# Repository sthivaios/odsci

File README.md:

# ODSCI

<div align="center">

  <h2 style="font-weight: bold;">An STM32-based USB interface for DS18B20 temperature sensors</h2>
  
</div>

## Getting Started - How to use ODSCI

**If you want to get started using ODSCI quickly, and don't care about the project, this is the only section of the README that matters to you.**

You can grab a pre-built CLI binary from the releases page for your platform/OS, or build from source. The CLI is written in Go and is located in the `/cli` directory.

Connect the ODSCI probe to your computer, and find the serial port that it uses (COM port on Windows, or a /dev/tty device on Linux and MacOS).

Then, you can use the `capture` command to save a given amount of samples as a CSV file.

```shell
./odsci --port THE_SERIAL_PORT_HERE --samples 100 --interval 10 --output "./output.csv"
```

The CLI has more features than just the `capture` command. Run `./odsci --help` for more information on the commands, or read the documentation.

## Introduction

ODSCI is an STM32-based USB interface for DS18B20 sensors. It stands for **O**neWire **DS**18B20 **C**omputer **I**nterface.

It connects to any computer through a USB-C port and exposes a USB CDC virtual serial port, through which
the MCU can send temperature readings back to the computer.

I am mainly working on this project, in order to teach myself Go (which the CLI uses), while also using it as
an excuse to attempt to write my own OneWire "driver" for the STM32 to communicate with the sensor.

## Project structure

You can find each "part" of ODSCI in its corresponding folder.

1. The firmware that runs on the STM32 is written in C and configured with CubeMX and uses CMake. It is located in the `/firmware` directory.

2. The hardware (PCB) is a KiCad project. It is located under `/hardware`.

3. The enclosure was designed in Fusion360. The project file, as well as any STL exports are located under the `/enclosure`.

4. The CLI is written in Go. You can find its source under `/cli`. I will attempt to cross-compile it for different platforms. Check the repo releases for pre-built binaries.

5. The docs are written with VitePress. You can find them under `/docs`.

## Contributing

You are welcome to report any issues that you find with any part of ODSCI, or open pull requests to fix them.

If you are actually contributing code to the project, make sure that you understand the license terms.

## Licensing

Different parts of the project are licensed under different licenses.

Under each directory, you will find a separate LICENSE file for that part of the project.

While that may seem a little confusing at first, please understand that some parts like the PCB simply
aren't very compatible with the usual licenses like MIT, GPL, etc.

See [LICENSE](LICENSE) for more info.

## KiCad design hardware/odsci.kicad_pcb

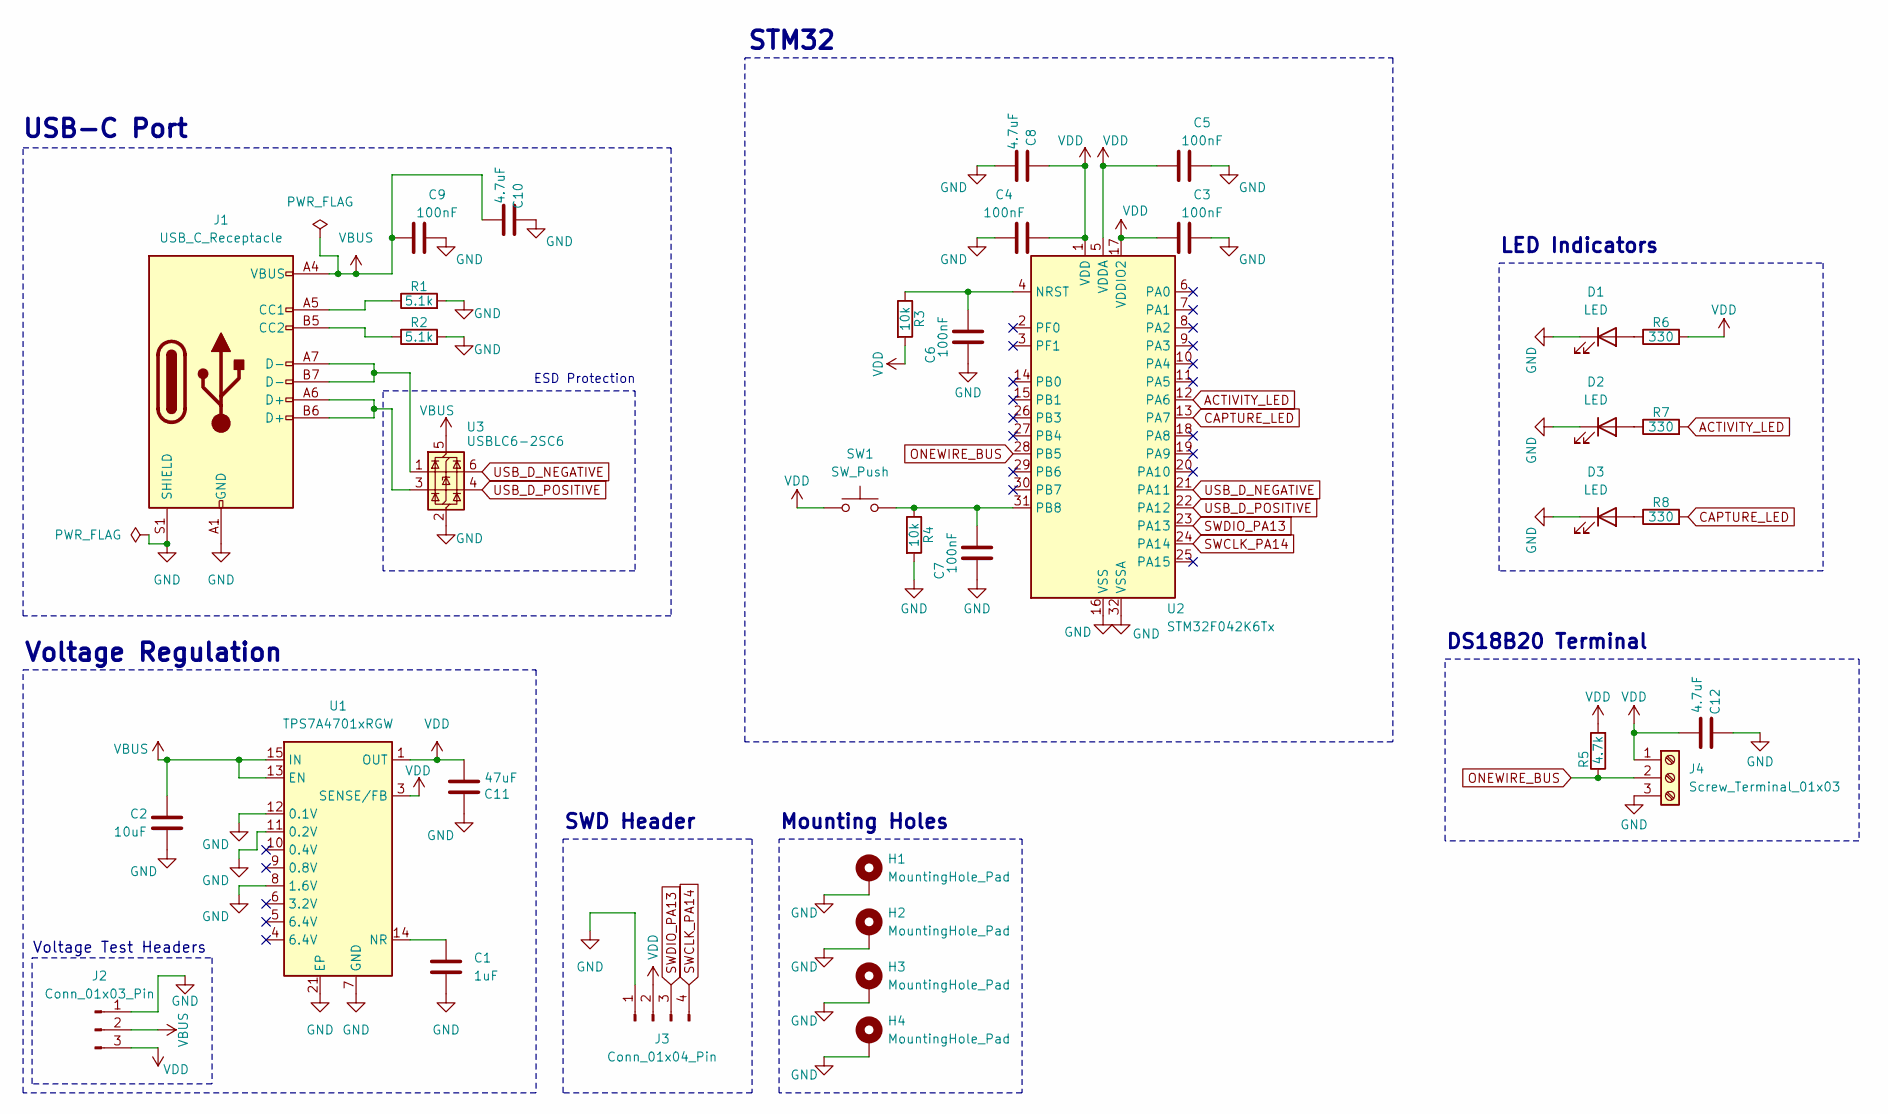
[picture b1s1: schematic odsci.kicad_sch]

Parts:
C1: 1uF; C_0805_2012Metric; LCSC C28323
C2: 10uF; C_0805_2012Metric; LCSC C15850
C3, C4, C5, C6, C7, C9: 100nF; C_0402_1005Metric; LCSC C1525
C8, C10, C12: 4.7uF; C_0805_2012Metric; LCSC C1779
C11: 47uF; C_0805_2012Metric; LCSC C16780
D1, D2, D3: LED; LED_D3.0mm
H1, H2, H3, H4: MountingHole_Pad; MountingHole_2.2mm_M2_Pad
J1: USB_C_Receptacle; USB_C_Receptacle_GCT_USB4105-xx-A_16P_TopMnt_Horizontal; LCSC C3020560
J2: Conn_01x03_Pin; PinHeader_1x03_P2.54mm_Vertical; LCSC C2915006
J3: Conn_01x04_Pin; PinHeader_1x04_P2.54mm_Vertical; LCSC C5184785
J4: Screw_Terminal_01x03; TerminalBlock_Phoenix_MPT-0,5-3-2.54_1x03_P2.54mm_Horizontal; LCSC C5288763
R1, R2: 5.1k; R_0402_1005Metric; LCSC C25905
R3, R4: 10k; R_0402_1005Metric; LCSC C25744
R5: 4.7k; R_0402_1005Metric; LCSC C25900
R6, R7, R8: 330; R_0402_1005Metric; LCSC C25104
SW1: SW_Push; SW_SPST_Omron_B3F-315x_Angled; LCSC C231320
U1: TPS7A4701xRGW; Texas_RGW0020A_VQFN-20-1EP_5x5mm_P0.65mm_EP3.15x3.15mm_Ther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; LCSC C90084
U2: STM32F042K6Tx; LQFP-32_7x7mm_P0.8mm; LCSC C69216
U3: USBLC6-2SC6; SOT-23-6; LCSC C7519

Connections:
ACTIVITY_LED: R7.2, U2.12 (PA6)
CAPTURE_LED: R8.2, U2.13 (PA7)
GND: C1.1, C2.1, C3.1, C4.1, C5.1, C6.2, C7.2, C8.1, C9.1, C10.2, C11.2, C12.2, D1.1 (K), D2.1 (K), D3.1 (K), H1.1, H2.1, H3.1, H4.1, J1.A1 (GND), J1.A12 (GND), J1.B1 (GND), J1.B12 (GND), J1.S1 (SHIELD), J2.1, J3.1, J4.3, R1.2, R2.2, R4.2, U1.7 (GND), U1.8 (1.6V), U1.11 (0.2V), U1.12 (0.1V), U1.21 (EP), U2.16 (VSS), U2.32 (VSSA), U3.2 (GND)
unnamed: D1.2 (A), R6.1
unnamed: D2.2 (A), R7.1
unnamed: D3.2 (A), R8.1
unnamed: J1.A5 (CC1), R1.1
unnamed: J1.B5 (CC2), R2.1
unnamed: J1.A6 (D+), J1.B6 (D+), U3.3 (I/O2)
unnamed: J1.A7 (D-), J1.B7 (D-), U3.1 (I/O1)
unnamed: C1.2, U1.14 (NR)
unnamed: C6.1, R3.1, U2.4 (NRST)
unnamed: C7.1, R4.1, SW1.2, U2.31 (PB8)
ONEWIRE_BUS: J4.2, R5.1, U2.28 (PB5)
SWCLK_PA14: J3.4, U2.24 (PA14)
SWDIO_PA13: J3.3, U2.23 (PA13)
USB_D_NEGATIVE: U2.21 (PA11), U3.6 (I/O1)
USB_D_POSITIVE: U2.22 (PA12), U3.4 (I/O2)
VBUS: C2.2, C9.2, C10.1, J1.A4 (VBUS), J1.A9 (VBUS), J1.B4 (VBUS), J1.B9 (VBUS), J2.2, U1.13 (EN), U1.15 (IN), U1.16 (IN), U3.5 (VBUS)
VDD: C3.2, C4.2, C5.2, C8.2, C11.1, C12.1, J2.3, J3.2, J4.1, R3.2, R5.2, R6.2, SW1.1, U1.1 (OUT), U1.3 (SENSE/FB), U1.20 (OUT), U2.1 (VDD), U2.5 (VDDA), U2.17 (VDDIO2)

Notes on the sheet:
STM32
ESD Protection
USB-C Port
Voltage Regulation
Voltage Test Headers
LED Indicators
SWD Header
Mounting Holes
DS18B20 Terminal

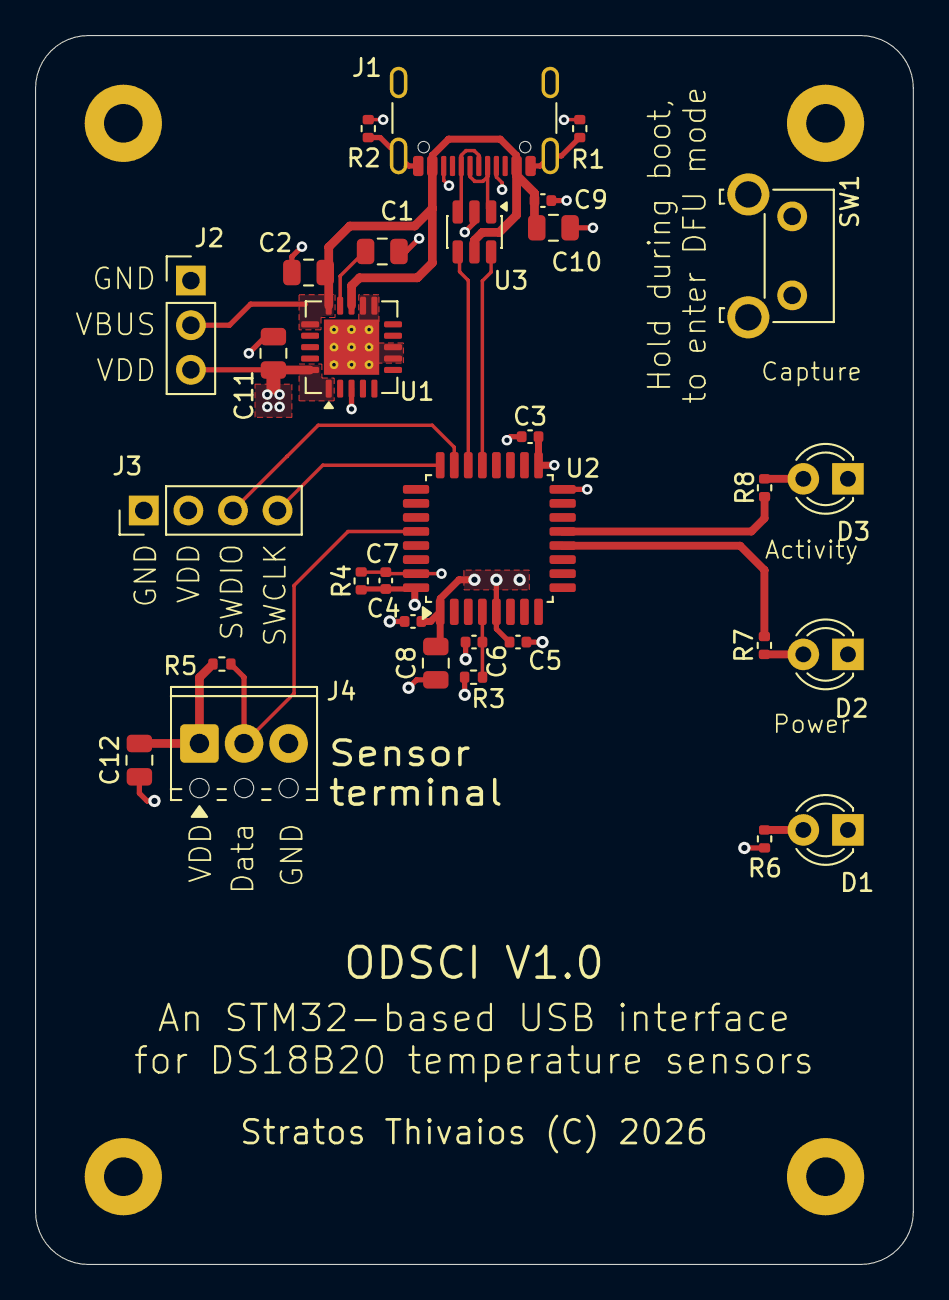
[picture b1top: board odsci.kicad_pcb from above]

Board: 4 copper layers, 50.0 x 70.0 mm, 35 parts (0 on the bottom side), 20 nets.

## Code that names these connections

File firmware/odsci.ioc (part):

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Mcu.Name=STM32F042K(4-6)Tx
Mcu.Package=LQFP32
Mcu.UserName=STM32F042K6Tx
PA11.Mode=Device
PA11.Signal=USB_DM
PA12.Mode=Device
PA12.Signal=USB_DP
PA13.Mode=Serial_Wire
PA13.Signal=SYS_SWDIO
PA14.Mode=Serial_Wire
PA14.Signal=SYS_SWCLK
PA6.GPIOParameters=GPIO_Label
PA6.GPIO_Label=ACTIVITY_LED
PA6.Signal=GPIO_Output
PA7.GPIOParameters=GPIO_Label
PA7.GPIO_Label=CLED_OR_ERROR_LED
PA7.Signal=GPIO_Output
PB5.GPIOParameters=GPIO_Label
PB5.GPIO_Label=ONEWIRE_BUS
PB5.Signal=GPIO_Input
RCC.SYSCLKFreq_VALUE=48000000
RCC.SYSCLKSource=RCC_SYSCLKSOURCE_HSI48
board=custom

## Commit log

2026-03-15 init
2026-03-17 add firmware license file
2026-03-17 add gitignore in firmware dir and the CubeMX ioc file
2026-03-17 CubeMX generated files
2026-03-18 add onewire driver
2026-03-18 onewire_write_bit() and onewire_read_bit()
2026-03-18 onewire_write_byte() and onewire_read_byte()
2026-03-18 add the higher level onewire functions
2026-03-18 fix minor stuff
2026-03-18 fix dumb include issues
2026-03-18 try to read the sensor in main.c
2026-03-18 make temperature variable global
2026-03-18 oops i got rid of the HAL_Delay accidentally
2026-03-18 command handler now receives stuff
2026-03-19 attempt to handle a command
2026-03-19 add a HAL_Delay in the main loop
2026-03-19 includes and stuff
2026-03-19 add the "-u _printf_float" linker flag
2026-03-19 command error handling
2026-03-19 use strcasecmp instead of strcmp
2026-03-19 get_info version cmd
2026-03-19 handle commands
2026-03-19 copyright headers
2026-03-20 remove random unused var
2026-03-20 configure PA6 and PA7 for leds
2026-03-20 change led labels in mx
2026-03-20 led control
2026-03-20 cli: go.mod
2026-03-20 cli: init main.go
2026-03-20 cli: add license
2026-03-20 cli: go.sum and go.mod
2026-03-20 cli: cobra init
2026-03-20 add packages
2026-03-20 cli: rootcmd description and desclaimer footer
2026-03-20 cli: init capture cmd
2026-03-20 cli: show cmd for gpl details
2026-03-20 cli: dependencies
2026-03-20 cli: capture cmd working at a low level
2026-03-20 cli: error handling
2026-03-20 cli: scan command
2026-03-20 cli: file organization
2026-03-21 cli: exit capture cmd gracefully on ctrl+c
2026-03-21 cli: minor bug and typo
2026-03-21 firmware: change cdc descriptors, fix bug
2026-03-21 cli: export as csv
2026-03-21 hardware: init kicad project
2026-03-21 hardware: schematic completed
2026-03-21 hardware: route pcb
2026-03-21 hardware: add mounting holes to pcb
2026-03-22 hardware: add a few decoupling caps
2026-03-22 hardware: layout of pcb
2026-03-22 hardware: fix mounting hole positions
2026-03-22 hardware: fully reroute and change pcb's layout
2026-03-24 hardware: update silkscreen, tiny layout changes
2026-03-24 hardware and schematic: add LCSC part number for switch
2026-03-24 hardware and schematic: update USB-C connector LCSC part number
2026-03-25 hardware: fix position of LEDs on the pcb to match enclosure
2026-03-28 hardware and schematic: update STM32 LCSC part number
2026-03-29 add CLED_IS_FOR_ERRORS_INSTEAD symbol
2026-03-29 make CLED commands depend on the CLED_IS_FOR_ERRORS_INSTEAD symbol
2026-03-29 use error indicator in different places
2026-03-29 fix includes
2026-03-29 remove leftover test from usbd_cdc_if.c
2026-03-29 report the CLED_IS_FOR_ERRORS_INSTEAD flag in GET_INFO
2026-03-29 bump major version as its a breaking change
2026-03-29 add firmware release script
2026-03-29 configure cmake to export .bin and .hex too
2026-03-29 github actions: firmware-release.yaml
2026-03-29 github actions: firmware-release.yaml: use local runner
2026-03-29 firmware release script: use master not main as the default branch
2026-03-29 firmware release script: fix bug cause i suck at bash
2026-03-29 firmware release script: add tag annotation
2026-03-29 firmware release action: change working dir
2026-03-29 add crc.c file
2026-03-29 create crc8 function
2026-03-29 implement crc
2026-03-29 report crc error in terminal if crc error occurs
2026-03-29 firmware release action: bug fixes
2026-03-29 bump firmware version: 1.0.0 to 1.1.0
2026-03-29 firmware release workflow: more bugs, we love github actions lol
2026-03-29 firmware release workflow: permission issue
2026-03-29 firmware release workflow: rename files before releasing
2026-03-29 firmware release workflow: im dumb
2026-03-29 firmware release workflow: clearly workflows arent my thing, more issue fixes
2026-03-29 changelog
2026-03-29 update to the github firmware release workflow
2026-03-29 this is so embarrassing lol
2026-03-29 minor changes to the github workflow again
2026-03-29 Restore cli directory from old branch
2026-03-29 cli: add version command, add a cli-release workflow
2026-03-29 cli: trigger workflow on dispatch for testing
2026-03-29 cli: oopsie
2026-03-29 cli: remove the scan command
2026-03-29 cli: fix ci/cd
2026-03-29 cli: changelog
2026-03-29 cli: ci/cd change trigger to only work on cli tags
2026-03-29 cli: add release.sh helper script
2026-03-29 cli: fix small bug in the release.sh script
2026-03-29 cli: fix minor ci/cd awk bug
2026-03-29 cli: more ci/cd bugs lol yay
2026-03-29 cli: more ci/cd bugs
2026-03-29 cli: more ci/cd bugs lol
2026-03-29 cli: more ci/cd bugs, i need a devops engineer lol
2026-03-29 cli: more ci- yeah you get the idea
2026-03-29 ci/cd: bump go releaser version
2026-03-29 ci/cd: fix goreleaser config for v2
2026-03-29 ci/cd: im gonna die lmao
2026-03-29 ci/cd: do i even bother with this anymore
2026-03-29 ci/cd: this actually might be a goreleaser issue not mine
2026-03-30 ci/cd: custom cli workflow without goreleaser
2026-03-30 ci/cd: oops forgot to give it write perms
2026-03-30 ci/cd: also build the linux binary for the cli, not only darwin and windows
2026-03-30 cli: add the read command
2026-03-30 cli: restructure read command for better readability and make code reusable as a func
2026-03-31 cli: helper function to clear the serial buffer
2026-03-31 cli: board info check function
2026-03-31 cli: read command: add the no-log flag
2026-03-31 cli: show timestamp in the read command
2026-03-31 cli: move ReadTemperature func into separate utils file
2026-03-31 cli: capture command: only enable CLED when the flag is set in firmware
2026-03-31 cli: read cmd: just some restructuring in the file mostly
2026-03-31 cli: minor bug fixes and forgotten debug lines
2026-03-31 ci/cd: release script now checks changelog first
2026-03-31 ci/cd: tiny changes to the release script
2026-03-31 chore: add readme latest version badges
2026-03-31 cli: make port and output flags required in read and capture cmds
2026-03-31 chore: update readme a bit
2026-03-31 chore: v1.1.1 CLI changelog
2026-03-31 ci/cd: tiny update to the release naming scheme
2026-03-31 firmware: readme
2026-04-01 chore: center top part of the readme
2026-04-01 oopsie lol
2026-04-01 firmware: fix minor bug that could cause a race condition
2026-04-01 cli: add flag for using iso8601 timestamps in the capture command
2026-04-01 cli: fix minor bug and update changelog
2026-04-01 cli: add c-to-f util function
2026-04-01 cli: oops, export ConvertCelciusToFahrenheit func
2026-04-01 cli: capture cmd: also store the fahrenheit value
2026-04-01 cli: read cmd: also convert and store as deg kelvin
2026-04-01 cli: update types.go
2026-04-01 cli: read cmd: update csv write function to store as kelvin too
2026-04-01 cli: read cmd: add unit selection
2026-04-01 cli: update changelog
2026-04-02 cli: `read` cmd: format to string propely before printing output
2026-04-02 cli: fix fahrenheit conversion
2026-04-02 cli: read cmd: print unit too
2026-04-02 cli: read cmd: fix bug where temperature wouldnt update with the --watch flag
2026-04-02 cli: read cmd: show difference from last read
2026-04-02 cli: update error messages to remove references to the scan cmd which is now gone
2026-04-02 cli: capture cmd: fix timestamp not converting to a string properly
2026-04-02 cli: update to schollz/progressbar v3
2026-04-03 cli: oops minor bug in the read cmd
2026-04-03 firmware: improve error handling when getting temperature
2026-04-03 firmware: changelog
2026-04-05 firmware: handle command buffer overflows better
2026-04-05 cli: read cmd: fix multiple bugs with the temperature conversion
2026-04-05 cli: chore: remove leftover goreleaser.yaml file - this isnt using goreleaser at all anymore
2026-04-06 firmware: configure iwdg in cubemx
2026-04-06 firmware: show iwdg reset status in the GET_INFO command
2026-04-06 firmware: set the IWDG status in from main.c so command handler can read it
2026-04-06 cli: detect iwdg reset and print advisory
2026-04-06 firmware: USB descriptors and serial number stuff
2026-04-06 firmware: USB descriptors
2026-04-06 firmware: chore: changelog
2026-04-06 cli: decode serial string too in board check
2026-04-06 cli: iwdg advisory: print actual serial number
2026-04-06 cli: change board check info decode approach
2026-04-06 cli: fix spacing after the iwdg advisory
2026-04-06 cli: chore: changelog
2026-04-06 cli: utils.ReadTemperature function now handles errors better
2026-04-07 CLI: print CRC errors and advisories in read and capture cmds
2026-04-07 cli: remove forgotten commented line lol
2026-04-07 chore: changelog, bump version in version.h
2026-04-07 chore: changelog, bump cli version to 1.2.0
2026-04-07 ci/cd: firmware release script: fix minor issue where release names had two v's like vv1.2.0
2026-04-07 ci/cd: cli release script: fix minor issue where release names had two v's like vv1.2.0
2026-04-14 chore: remove old ioc file
2026-04-14 firmare: new cubemx ioc file
2026-04-14 firmware: cleanup and replace files with their stm32f0 equivalent
2026-04-14 firmware: more cleanup
2026-04-14 firmware: enable iwdg in mx
2026-04-14 firwmare: more porting work lmao im too lazy to write proper commit messages
2026-04-14 chore: update firmware release workflow a bit
2026-04-14 chore: changelog.md
2026-04-14 chore: update version string in firmware
2026-04-14 firmware: update IWDG timeout, update changelog
2026-04-14 cli: add the silence-advisories flag, inform user about amount of valid samples captured, update changelog
2026-04-14 firmware: chore: update version string in version.h

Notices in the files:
hardware/odsci.kicad_pcb:
CERN Open Hardware License v2 - Strongly Reciprocal
Copyright © 2026 Stratos Thivaios
Stratos Thivaios (C) 2026
